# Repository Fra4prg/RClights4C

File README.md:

# RClights4C
4 channel lightning module for RC models

The main controller electronic weighs only 1.4g and is populated on a 25 x 28 mm PCB.
In addition you need some wiring and LEDs depending on your configuration.
Enameled wire is the best choice for light weight models.
The module is suitable for big models as well as for ultra micro models such as planes, helicopters, ships, cars, ...

For RC control you only need one channel for controlling 4 independent output channels.
This is implemented as 16 discrete binaary coded channel values.
The RC channel can be mixed on the transmitter, e.g. from 4 switches.
The process how to do this is described in the documentation file (currently only in german).

The lightning patterns of eac output (number, length and pauses) can be programmed via transmitter.
E.g. you can use one channel for landing lights as permanent, another channel for strobe lights flashing 3 times every second, one for navigation lights and one for ACL lights.

If you don't have any free RC channel you can also connect a button to the RC input instead of an RC receiver.
With this you can switch through activating all 4 output channels subsequently.

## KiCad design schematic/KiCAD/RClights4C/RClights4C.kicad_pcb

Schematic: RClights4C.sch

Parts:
B1, B2, B3, B4, B5, B6: Jumper; SolderJumper-2_P1.3mm_Open_RoundedPad1.0x1.5mm
C2: 100n; C_0805_2012Metric
I1: ATtiny85-20SU; SOIJ-8_5.3x5.3mm_P1.27mm
R1, R4, R6, R8, R11, R14, R15, R16: 1k; R_1206_3216Metric
R17: 10k; R_0805_2012Metric
T1, T2, T3, T4: DTC114E; SOT-23
X1: Supply+; PinHeader_1x02_P2.54mm_Horizontal
X8: LEDs; PinHeader_1x08_P2.54mm_Horizontal
X9: Battery; PinHeader_1x02_P2.54mm_Horizontal
X14: RC; PinHeader_1x03_P2.54mm_Horizontal
X15: ISP; PinHeader_2x03_P1.27mm_Vertical

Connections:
+BATT: X1.1, X1.2, X9.1
/MISO: I1.6 (PB1), T3.1, X15.1
/MOSI: I1.5 (AREF/PB0), T4.1, X15.4
/RESET: I1.1 (~RESET~/PB5), X15.5
/SCK: I1.7 (PB2), R17.1, X15.3
GNDD: C2.2, I1.4 (GND), T1.2, T2.2, T3.2, T4.2, X9.2, X14.1, X15.6
unnamed: B1.1, R8.2, T3.3
unnamed: B1.2, B2.1, R11.2
unnamed: B2.2, B3.1, R14.2, T4.3
unnamed: B3.2, B4.1, R15.2
unnamed: B4.2, B5.1, R16.2
unnamed: B5.2, B6.1, R1.2, T1.3
unnamed: B6.2, R4.2, R6.2, T2.3
unnamed: I1.2 (XTAL1/PB3), T2.1
unnamed: I1.3 (XTAL2/PB4), T1.1
unnamed: R1.1, X8.6
unnamed: R4.1, X8.7
unnamed: R6.1, X8.8
unnamed: R8.1, X8.1
unnamed: R11.1, X8.2
unnamed: R14.1, X8.3
unnamed: R15.1, X8.4
unnamed: R16.1, X8.5
unnamed: R17.2, X14.3
VCC: C2.1, I1.8 (VCC), X14.2, X15.2

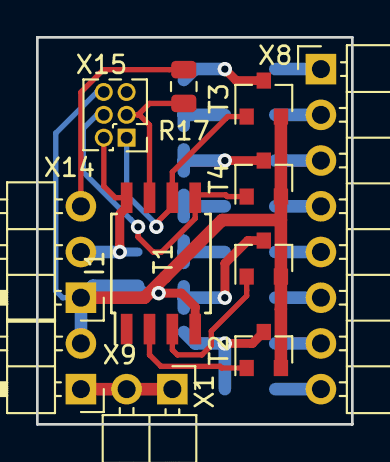
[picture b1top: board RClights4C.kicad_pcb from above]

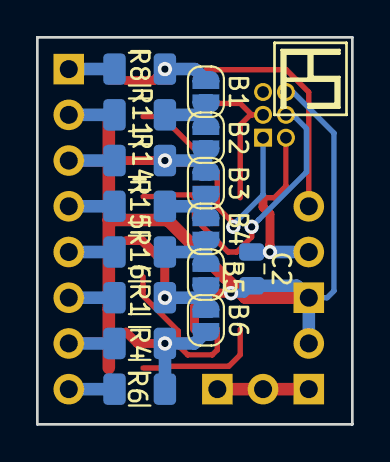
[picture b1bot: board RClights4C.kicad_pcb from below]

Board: 2 copper layers, 17.5 x 21.5 mm, 26 parts (15 on the bottom side), 25 nets.

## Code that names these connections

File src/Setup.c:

/*------------------------------------------------------------------------------
 * Setup.c
 * generic initialisation routines for AeroLight_4C
 *
 * Copyright (c) 2014 Frank Scholl - MegaProjects@t-online.de
 *
 * ATTINY45 @ 8 MHz
 *
 * This program is free software; you can redistribute it and/or modify
 * it under the terms of the GNU General Public License as published by
 * the Free Software Foundation; either version 2 of the License, or
 * (at your option) any later version.
 *------------------------------------------------------------------------------
 */

 
 //  Include files
#include "all_headers.h"


/*------------------------------------------------------------------------------
 * Included Functions and ISR
 *  @details  -
 *  @param    -
 *  @return   -
 *------------------------------------------------------------------------------
 */

 
/*------------------------------------------------------------------------------
 * global variables
 *------------------------------------------------------------------------------
 */




/*------------------------------------------------------------------------------
 * Configure Ports (set direction)
 *  @details  -
 *  @param    -
 *  @return   -
 *------------------------------------------------------------------------------
 */
void config_ports (void)
{
	
	//Set Direction Registers (Input/Output) default set to Input (0x00) 
	//------------------------------------------------------------------
	
	// *** configure PORTB ***
	// Set output direction registers
	// PB.0 = (out, low)		LEDs for Navigation Lights
	// PB.1 = (out, low)		LEDs for ACL / Beacon
	// PB.2 = (in, Pullup)		RC signal
	// PB.3 = (out, low)		LEDs for Strobe Lights
	// PB.4 = (out, low)		LEDs for Landing Lights
	// PB.5 = (RESET in)
	//
	// Set input pullups
	PORTB = (0<<PB0)  | (0<<PB1)  | (1<<PB2)  | (0<<PB3)  | (0<<PB4)  | (0<<PB5);
	// Set directions
	DDRB  = (1<<DDB0) | (1<<DDB1) | (0<<DDB2) | (1<<DDB3) | (1<<DDB4) | (0<<DDB5);

}


/*------------------------------------------------------------------------------
 * Configure External Interrupts
 *  @details  -
 *  @param    -
 *  @return   -
 *------------------------------------------------------------------------------
 */
void config_extint (void)
{
	// *** MCU Control Register ***
	// SC01, ISC00: Interrupt Sense Control 0 Bit 1 and Bit 0
	//MCUCR = (0<<BODS) | (0<<PUD) | (0<<SE) | (0<<SM1) | (0<<SM0) | (0<<BODSE)  | (0<<ISC01)  | (0<<ISC00); // complete register
	//xxxxxxxxxxxxxxxxxxxxxxxxxxxxxxxxxxxxxxxxxxxxxxxxxxxxxxxxxx only change these bits (other bits used for different function)
	//                                               v            v          --> only bits used in this unit
	MCUCR = (MCUCR & ~((1<<ISC01) | (1<<ISC00))) | ((1<<ISC01) | (0<<ISC00));

	// *** GIMSK  General Interrupt Mask Register ***
	// INT0: External Interrupt Request 0 Enable
	// PCIE: Pin Change Interrupt Enable
	GIMSK = (0<<INT0) | (1<<PCIE); // complete register

	// *** GIFR  General Interrupt Flag Register ***
	// INTF0: External Interrupt Flag 0
	// PCIF: Pin Change Interrupt Flag
	//GIFR = (0<<INTF0) | (0<<PCIF); // complete register

	// *** PCMSK  Pin Change Mask Register ***
	// PCINT5:0: Pin Change Enable Mask 5:0
	PCMSK = (0<<PCINT5) | (0<<PCINT4) | (0<<PCINT3) | (1<<PCINT2) | (0<<PCINT1) | (0<<PCINT0); // complete register


}


/*------------------------------------------------------------------------------
 * setup uC
 *  @details  -
 *  @param    -
 *  @return   -
 *------------------------------------------------------------------------------
 */
void setup (void)
{	
	//Init uC peripheral
	//-------------------
	config_ports();			// this configures the I/O ports

	TimerInit();
	
	config_extint();

	// reset button detection (set by 4ms timeout)
	button_release_count = 0;
	button_pressed_count = 0;
	button_was_read = true;
	button_state = BUTTON_NOT_AVAILABLE;

		
		// *** get saved values from EEPROM ***

//		flash(0b10000000, 10, 20, 50, false);  // =====================
//		long_delay_ms(1000);

/* compare complement does not work at first instance !!!!!!!!!!!!!?????????
		rd_EE = eeprom_read_byte(&EE_pattern_select);
		rd_EE_cp = eeprom_read_byte(&EE_pattern_select_cp);
		if (rd_EE == (~rd_EE_cp))  // check redundancy by complement
		{
			check=0; // dummy
		}


//		flash(0b10000000, 10, 20, 50, false);  // =====================
//		long_delay_ms(1000);

		LEDspeed = constrain(eeprom_read_byte(&EE_LEDspeed),SPEED_MIN,SPEED_MAX);
		eeprom_write_byte ( &EE_LEDspeed, LEDspeed);
		eeprom_write_byte ( &EE_LEDspeed_cp, ~LEDspeed);
*/

		// enable interrupts
		sei();
		
//		long_delay_ms(100);
}

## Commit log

2021-03-20 Initial update
2021-03-20 Readme picture added
2021-03-20 3x panel added
